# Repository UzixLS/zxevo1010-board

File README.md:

## ZXEVO.1010
10x10cm 2-layer PCB variant of [ZX Evolution](http://nedopc.com/zxevo/zxevo.php) project

Some random photos: [link](https://cloud.err200.net/index.php/s/73TR85tYZkMm8Ax?path=%2Fzxevo1010)

Tech specs:
- Fully compatible with ZX Evolution revC
- SD/microSD card slot
- PS/2 keyboard and mouse ports
- VGA video output
- VDAC2
- TSFM (mono output) powered by 2xYMF288
- [NeoGS](http://nedopc.com/gs/ngs.php)
- SounDrive (4-channel stereo covox)
- MIDI onboard synthesizer and output for external synthesizer
- WiFi ([ZiFi](http://zifi.vtrd.in/))
- RTC
- Tape input via 3.5 jack
- 1xDB-9 port for Sega-compatible joysticks
- USB Type C power supply
- Board optimized for G738 and G706 cases

### Changelog
#### Main PCB
* Rev.A - first release
* Rev.A1: - see [ERRATA](pcb_main/rev.A1/ERRATA.txt)!
    * enlarged ACEX's footprint
    * fixed IO led always on in baseconf - added C92 and D7
    * changed R66 from 390Ω to 2.2kΩ to reduce power led bightness
    * changed R52 and R58 from 27kΩ to 18kΩ for better VDAC2 mixing volume
    * slightly moved U18
    * some minor changes

#### Top PCB
* Rev.A - first release
* Rev.A1: - see [ERRATA](pcb_top/rev.A1/ERRATA.txt)!
    * added 51Ω R1 and R3 on DAC and MP3 clock signals to fix signal integrity issues
    * changed U9 from SN74LXC8T245PWR (which is unsuitable) to 74LVC245APW
    * changed R7 from 120Ω to 1kΩ to decrease LED brightness
    * changed R26 and R29 from 8.2kΩ to 18kΩ for better NeoGS mixing volume
    * changed R23 and R31 from 22kΩ to 15kΩ for better MIDI mixing volume
    * changed R65, R66, R67 and R68 from 8.2kΩ to 3.3kΩ for better PSG mixing volume (but this makes FM a unbalancy loud unfortunatelly)
    * added R50, R51, R61, C102, C103, C104 for VS10xx MP3 decoder
    * fixed swapped left-right sound channels
    * increased cutoff for CR2032 holder

### Useful software
* NedoOS (BaseConf): http://nedoos.ru/
* Wild Commander (TSConf): https://forum.tslabs.info/viewtopic.php?f=26&t=143
* ZiFi WiFi client (TSConf): http://zifi.vtrd.in/
* TSConf software library: https://prods.tslabs.info/
* Joystick configuration utility (TSConf): https://github.com/tslabs/zx-evo/tree/master/pentevo/soft/avrconf

### References
* ZX Evolution official site: http://nedopc.com/zxevo/zxevo.php

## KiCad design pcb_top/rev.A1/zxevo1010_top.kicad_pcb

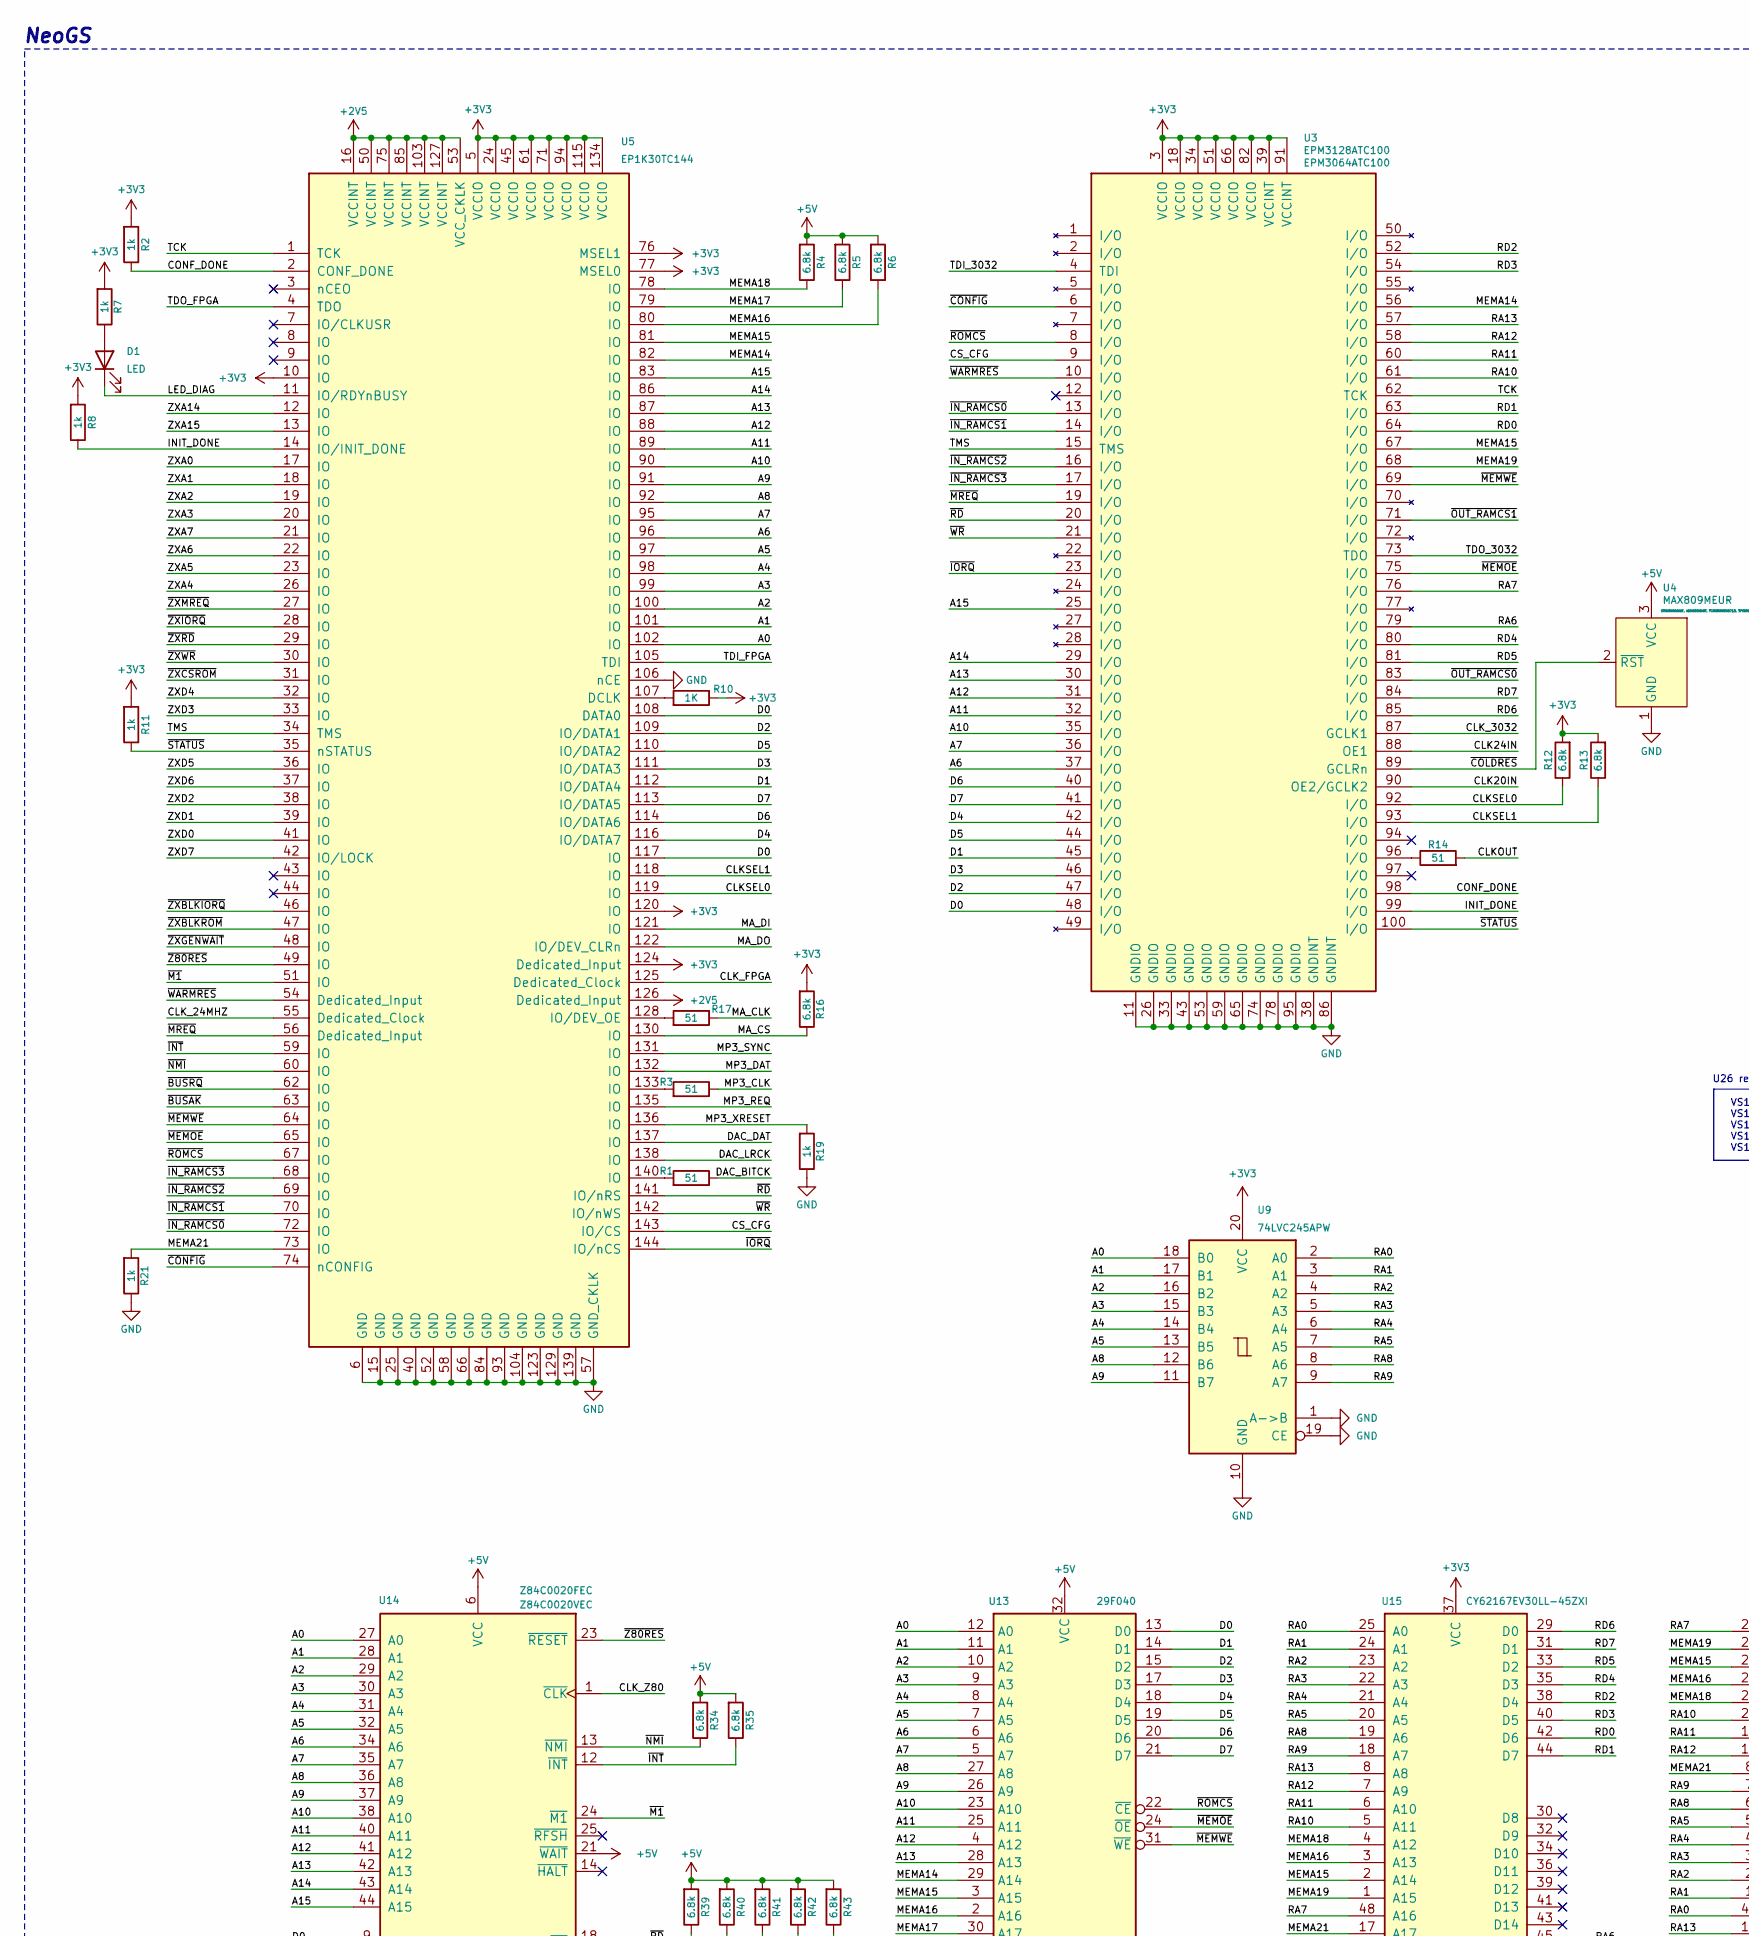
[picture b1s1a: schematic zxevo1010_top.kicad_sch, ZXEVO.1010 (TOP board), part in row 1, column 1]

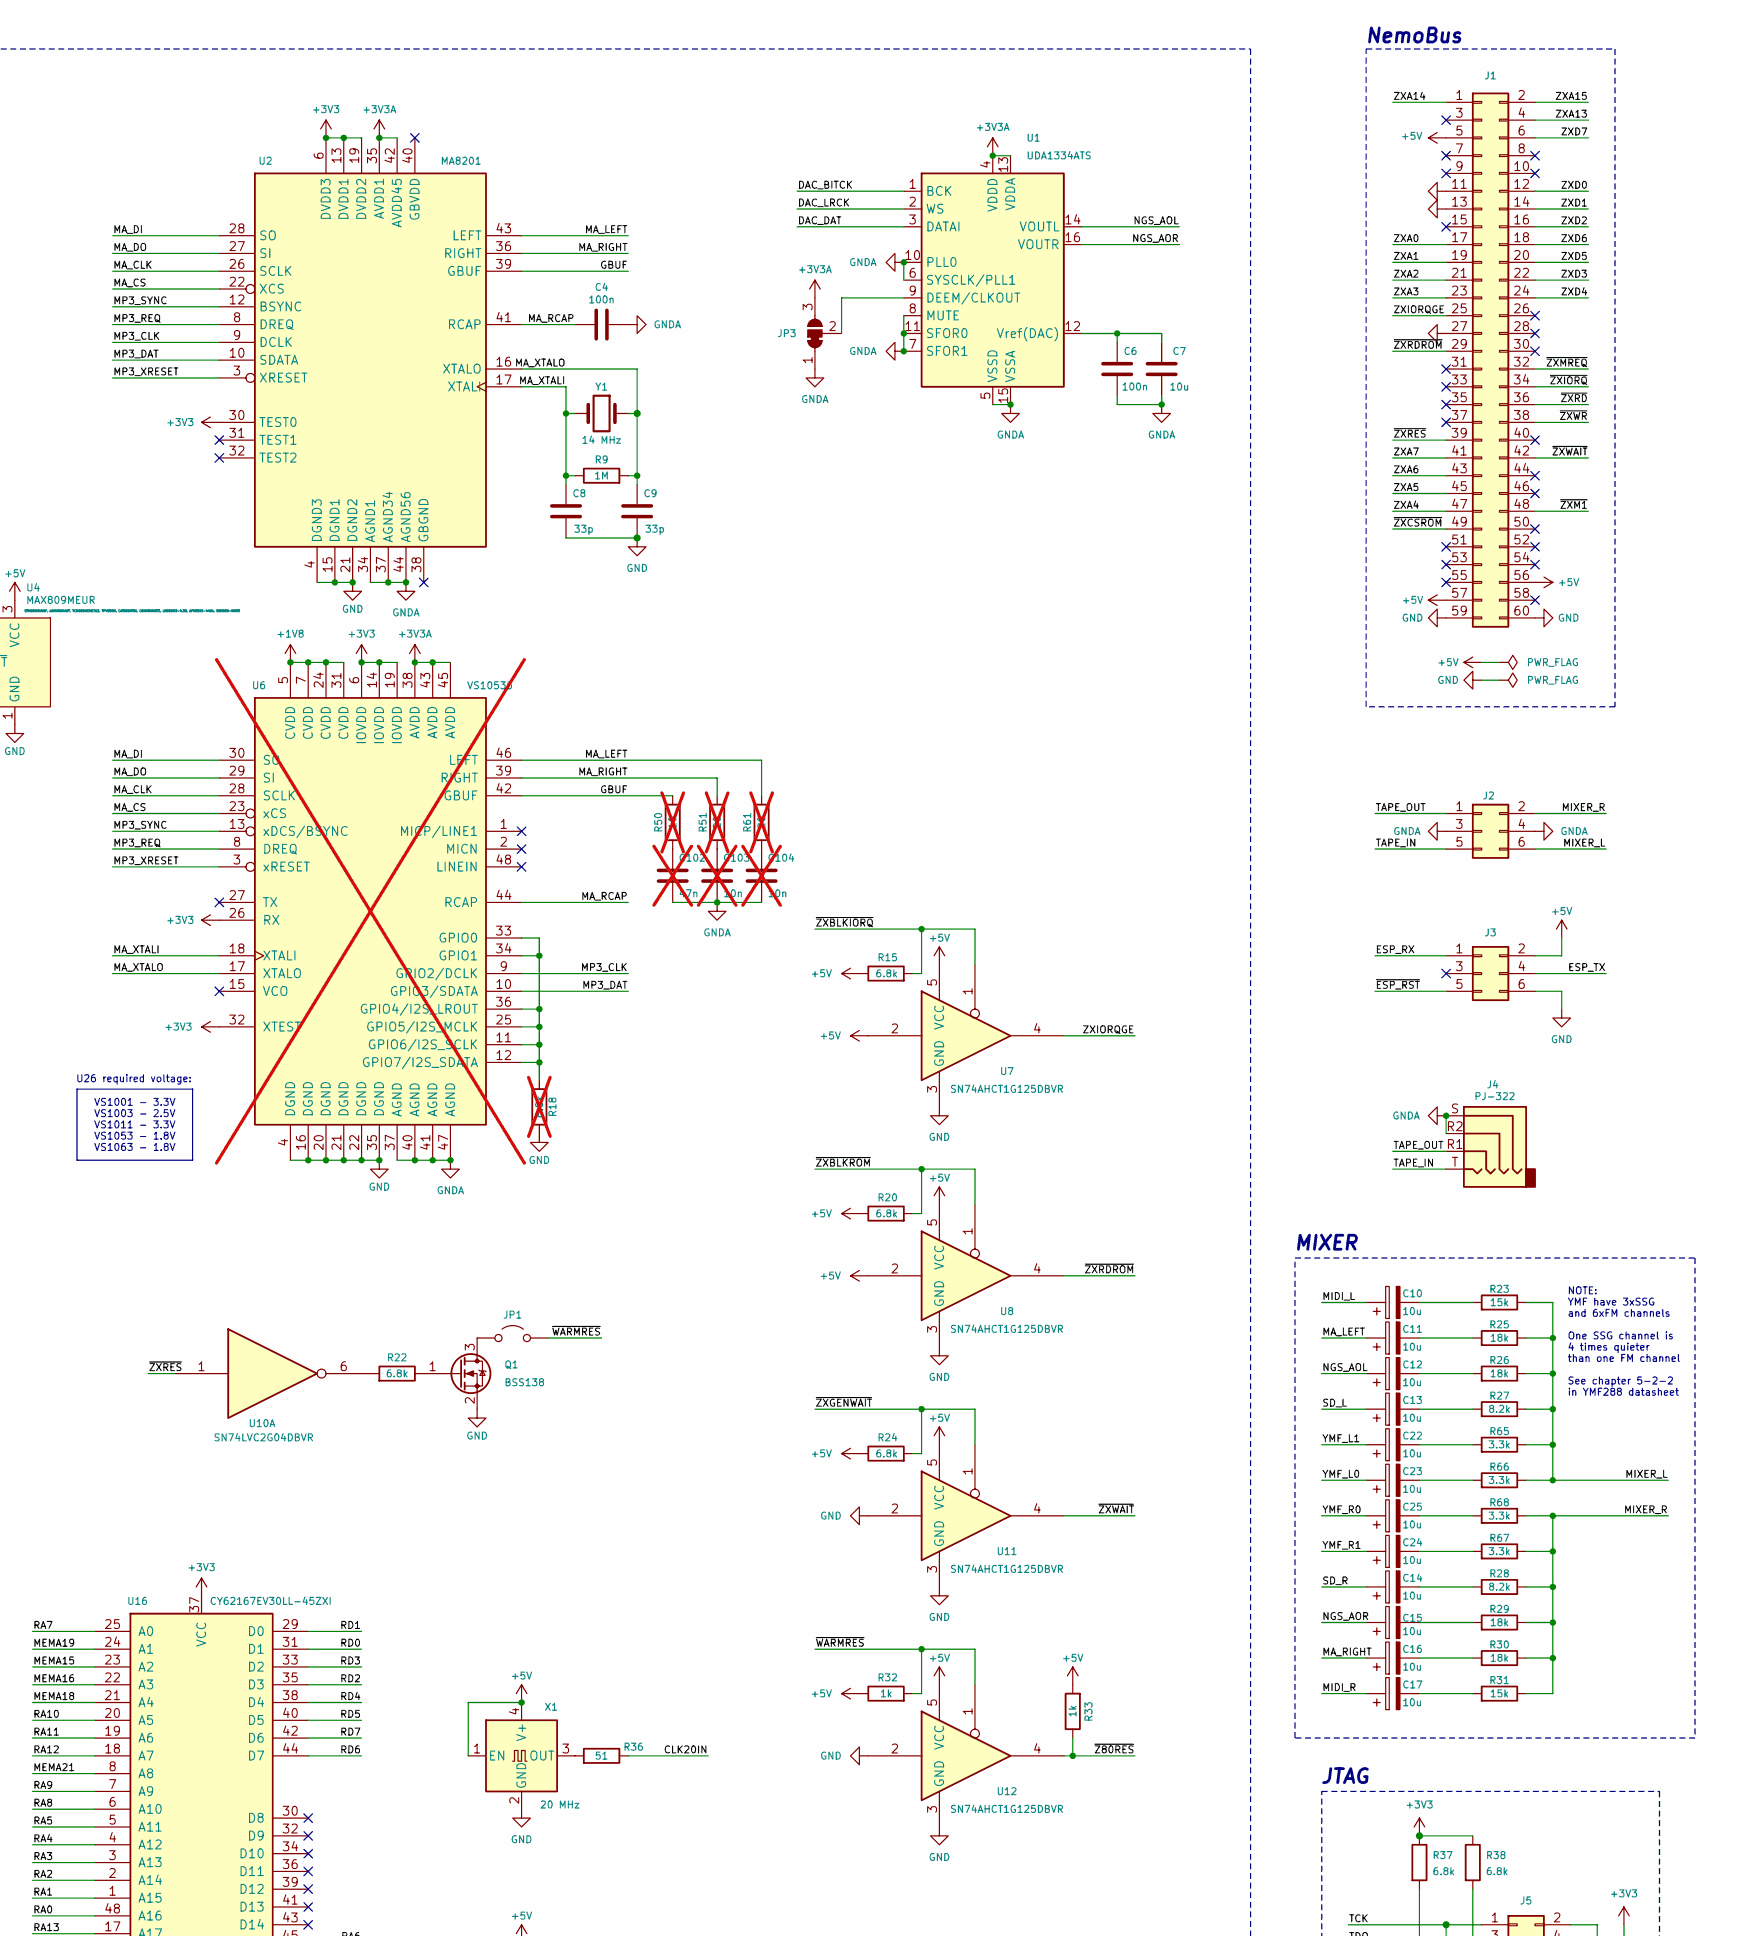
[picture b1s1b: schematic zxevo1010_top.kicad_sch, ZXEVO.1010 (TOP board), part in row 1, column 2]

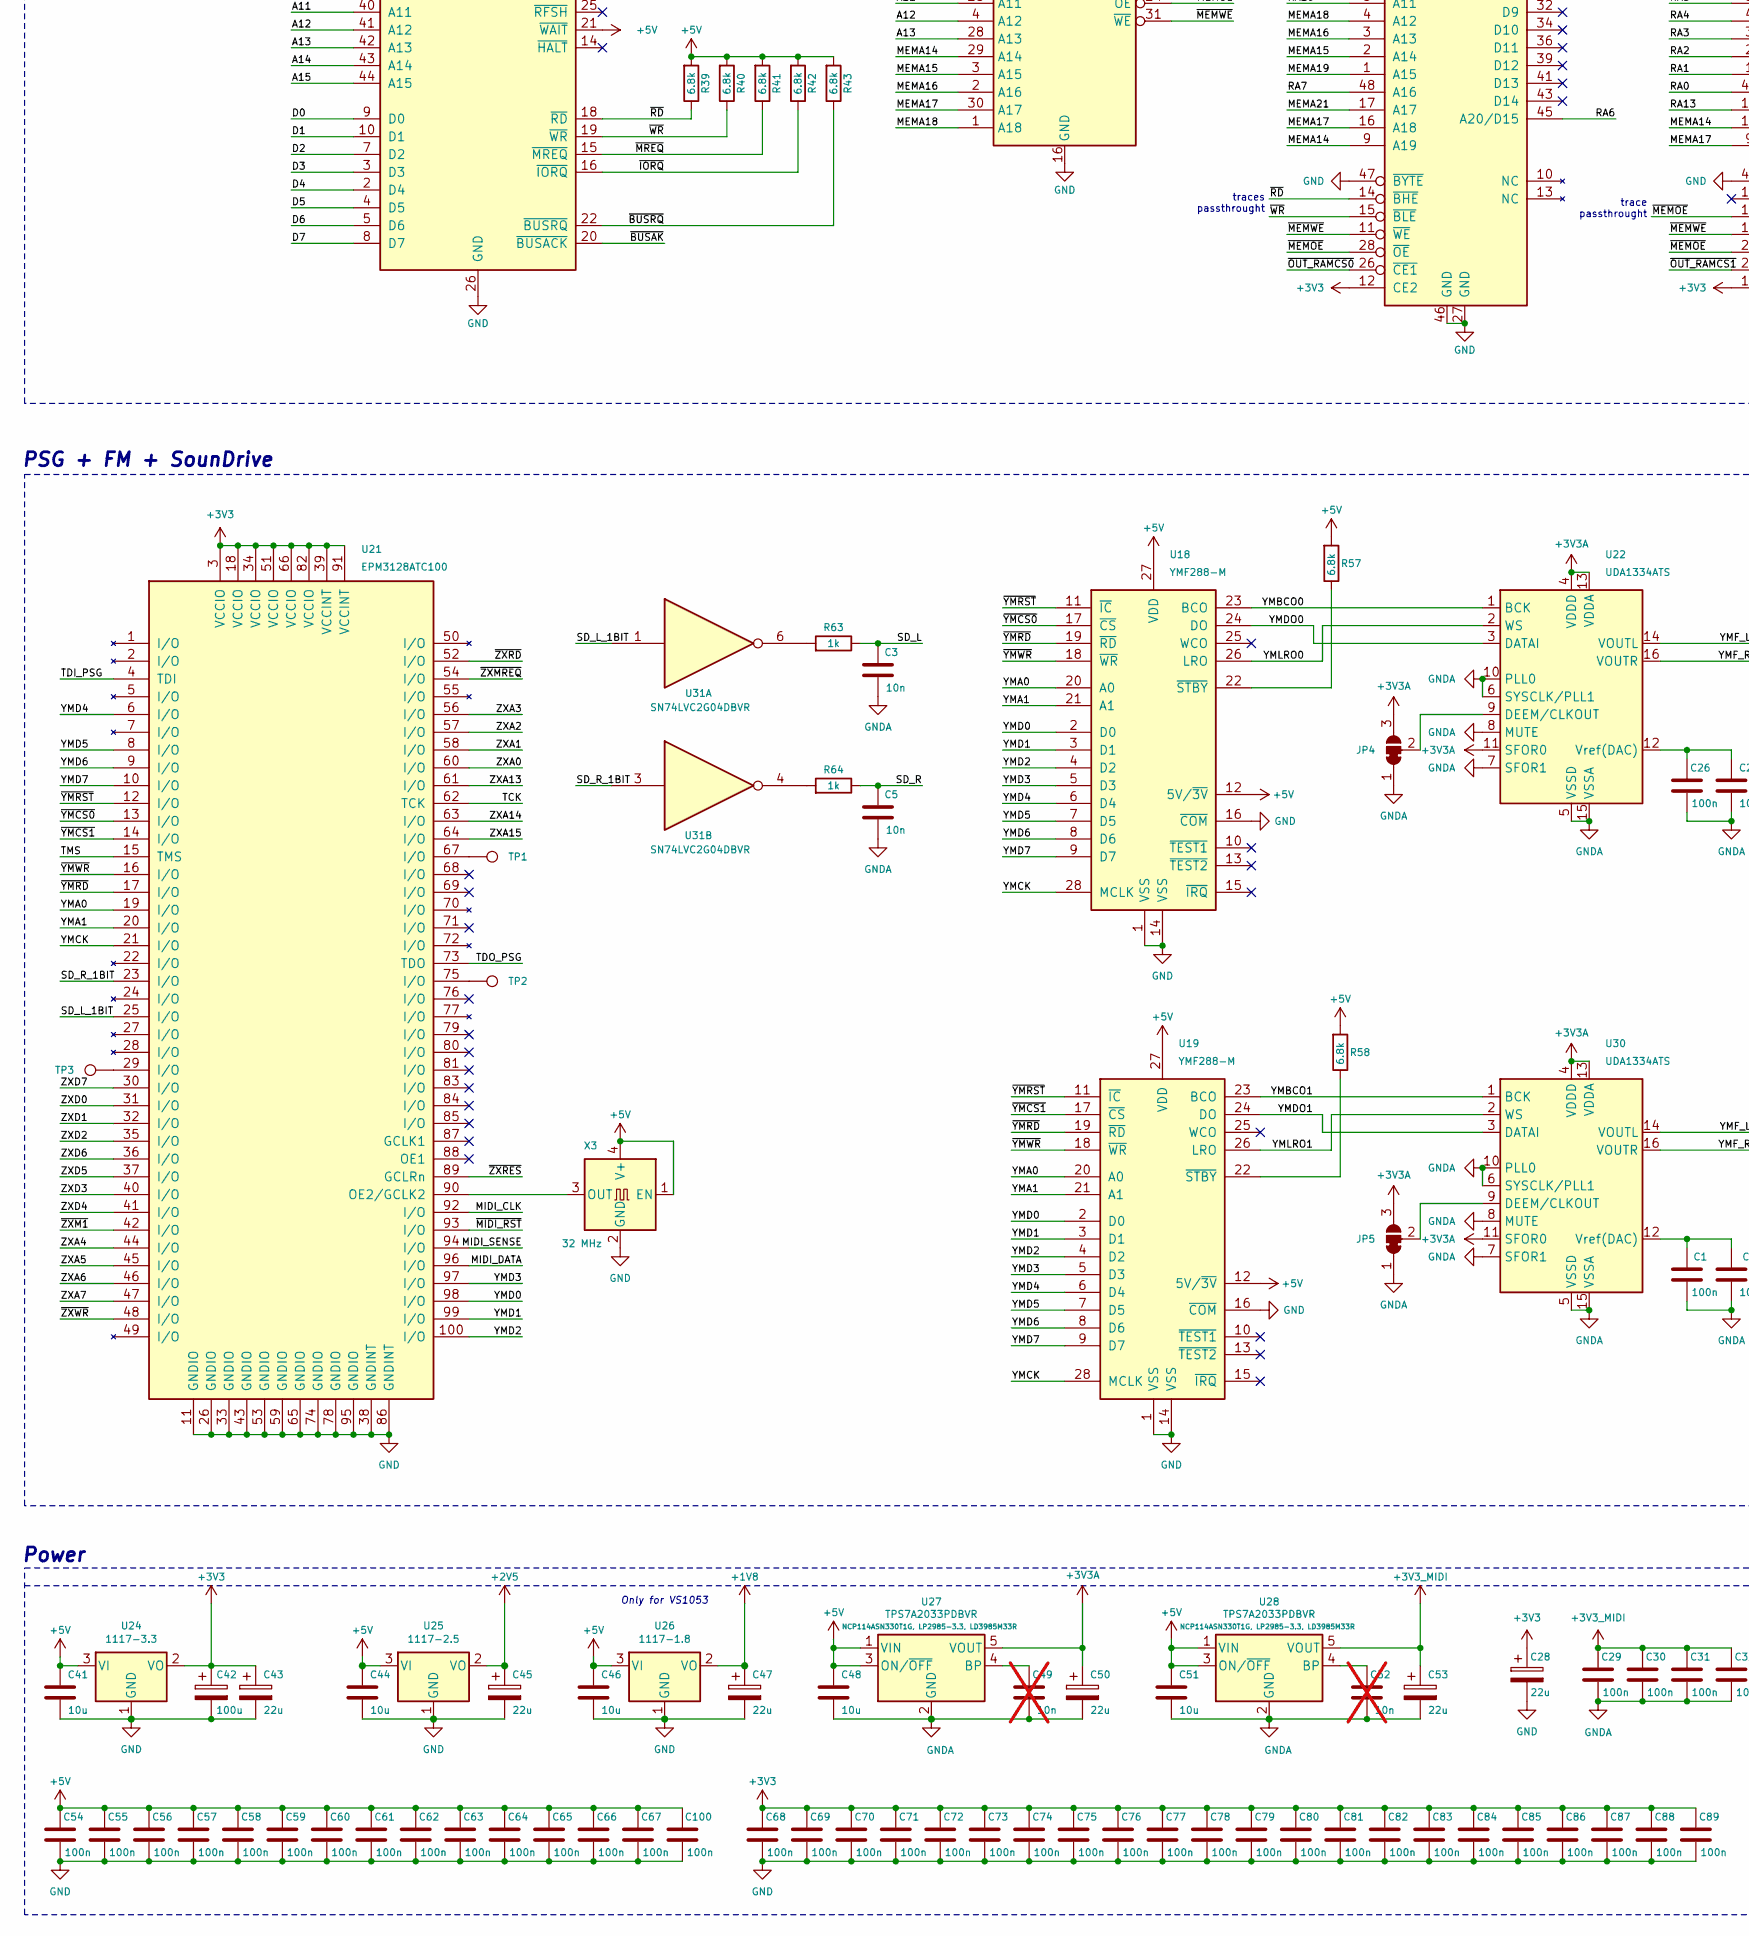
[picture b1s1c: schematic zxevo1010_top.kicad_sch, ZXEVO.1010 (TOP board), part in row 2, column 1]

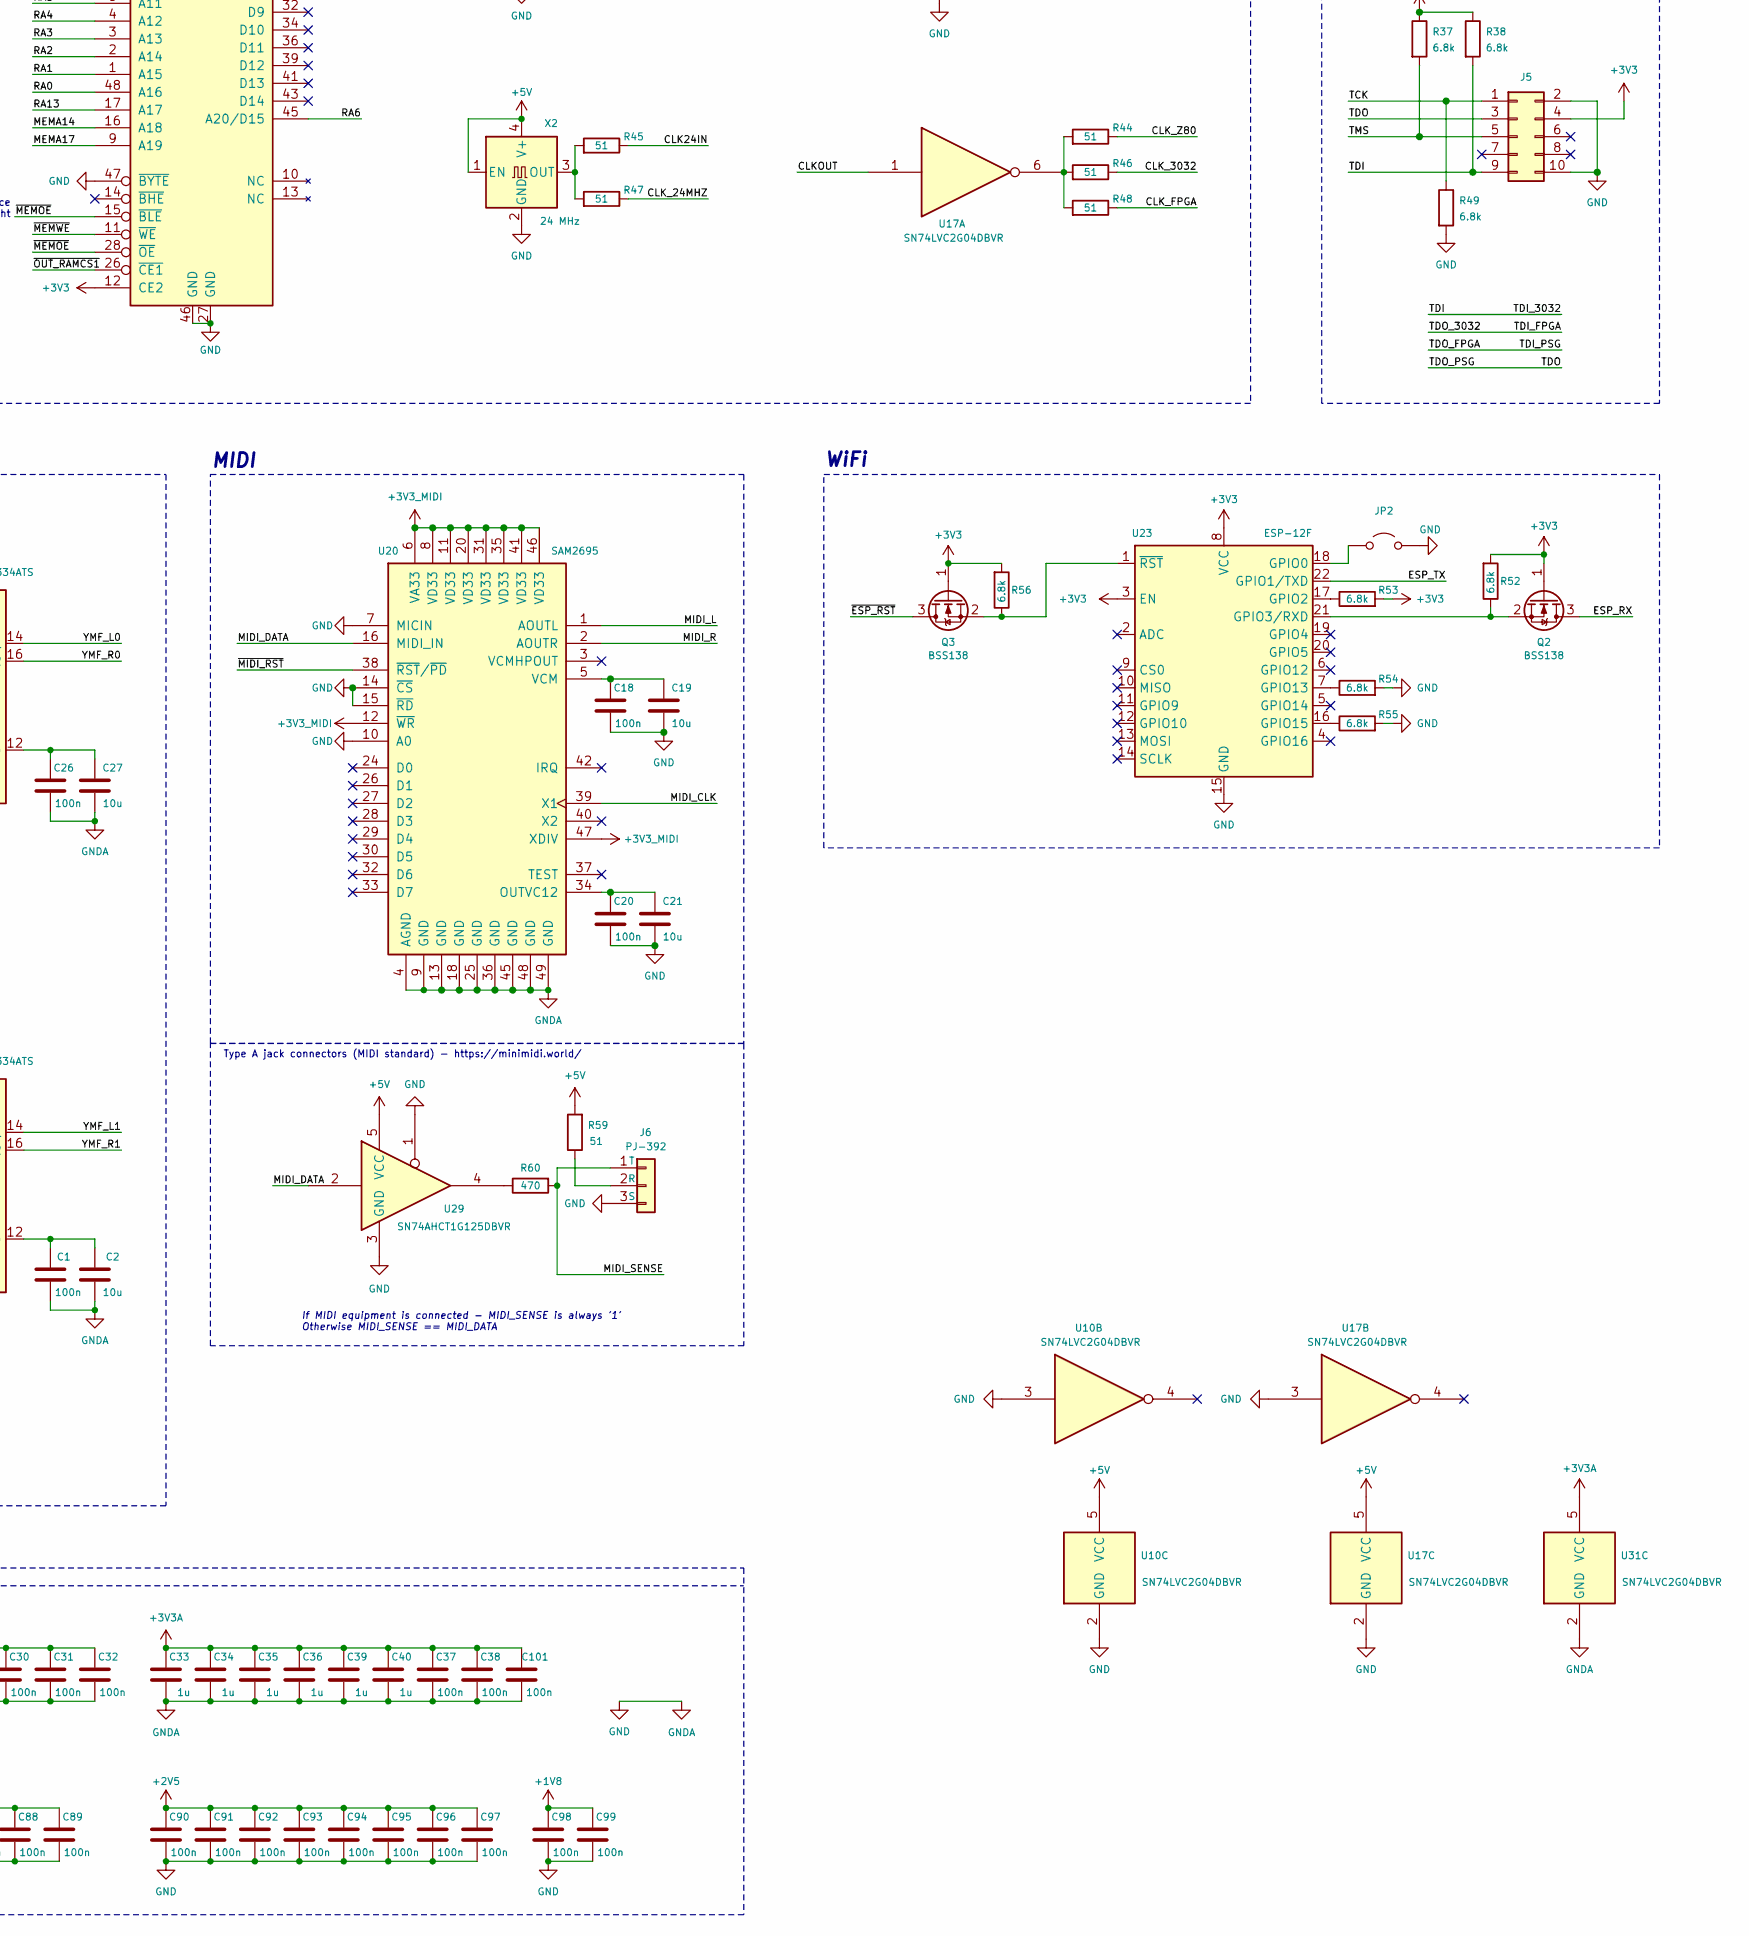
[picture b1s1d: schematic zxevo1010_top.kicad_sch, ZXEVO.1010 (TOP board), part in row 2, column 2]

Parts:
C1, C4, C6, C18, C20, C26, C29, C30, C31, C32, C37, C38, C54, C55, C56, C57, C58, C59, C60, C61, C62, C63, C64, C65, C66, C67, C68, C69, C70, C71, C72, C73, C74, C75, C76, C85, C86, C87, C88, C89, C98, C99, C100, C101: 100n; C_0603_1608Metric_Pad1.08x0.95mm_HandSolder
C2, C7, C19, C21, C27, C41, C44, C46, C48, C51: 10u; C_0805_2012Metric_Pad1.18x1.45mm_HandSolder
C3, C5: 10n; C_0603_1608Metric_Pad1.08x0.95mm_HandSolder
C8, C9: 33p; C_0603_1608Metric_Pad1.08x0.95mm_HandSolder
C10, C11, C12, C13, C14, C15, C16, C17, C22, C23, C24, C25: 10u; CP_EIA-3216-18_Kemet-A_Pad1.58x1.35mm_HandSolder
C28, C43, C45, C47, C50, C53: 22u; CP_EIA-3216-18_Kemet-A_Pad1.58x1.35mm_HandSolder
C33, C34, C35, C36, C39, C40: 1u; C_0603_1608Metric_Pad1.08x0.95mm_HandSolder
C42: 100u; CP_EIA-6032-28_Kemet-C_Pad2.25x2.35mm_HandSolder
C49, C52, C103, C104: 10n; C_0603_1608Metric_Pad1.08x0.95mm_HandSolder; not fitted
C77, C78, C79, C80, C81, C82, C83, C84, C90, C91, C92, C93, C94, C95, C96, C97: 100n; C_0805_2012Metric_Pad1.18x1.45mm_HandSolder
C102: 47n; C_0603_1608Metric_Pad1.08x0.95mm_HandSolder; not fitted
D1: LED; LED_0603_1608Metric_Pad1.05x0.95mm_HandSolder
J1: Conn_02x30_Row_Letter_First; PinHeader_2x30_P2.54mm_Vertical
J2, J3: Conn_02x05_Odd_Even; PinSocket_2x03_P2.54mm_Vertical
J4: PJ-322
J5: Conn_02x05_Odd_Even; PinHeader_2x05_P2.54mm_Vertical
J6: PJ-392; PinHeader_1x03_P2.54mm_Vertical
JP1, JP2: Jumper; PinHeader_1x02_P2.54mm_Vertical
JP3, JP4, JP5: SolderJumper_3_Bridged12; SolderJumper-3_P1.3mm_Bridged12_RoundedPad1.0x1.5mm
Q1, Q2, Q3: BSS138; SOT-23
R1, R3, R14, R17, R36, R44, R45, R46, R47, R48, R59: 51; R_0603_1608Metric_Pad0.98x0.95mm_HandSolder
R2, R7, R8, R11, R19, R21, R32, R33, R63, R64: 1k; R_0603_1608Metric_Pad0.98x0.95mm_HandSolder
R4, R5, R6, R12, R13, R15, R16, R20, R22, R24, R34, R35, R37, R38, R39, R40, R41, R42, R43, R49, R52, R53, R54, R55, R56, R57, R58: 6.8k; R_0603_1608Metric_Pad0.98x0.95mm_HandSolder
R9: 1M; R_0603_1608Metric_Pad0.98x0.95mm_HandSolder
R10: 1K; R_0603_1608Metric_Pad0.98x0.95mm_HandSolder
R18: 6.8k; R_0603_1608Metric_Pad0.98x0.95mm_HandSolder; not fitted
R23, R31: 15k; R_0603_1608Metric_Pad0.98x0.95mm_HandSolder
R25, R26, R29, R30: 18k; R_0603_1608Metric_Pad0.98x0.95mm_HandSolder
R27, R28: 8.2k; R_0603_1608Metric_Pad0.98x0.95mm_HandSolder
R50: 10; R_0603_1608Metric_Pad0.98x0.95mm_HandSolder; not fitted
R51, R61: 20; R_0603_1608Metric_Pad0.98x0.95mm_HandSolder; not fitted
R60: 470; R_0603_1608Metric_Pad0.98x0.95mm_HandSolder
R65, R66, R67, R68: 3.3k; R_0603_1608Metric_Pad0.98x0.95mm_HandSolder
TP1, TP2, TP3: TestPoint; TestPoint_Pad_D1.0mm
U1, U22, U30: UDA1334ATS; SSOP-16_4.4x5.2mm_P0.65mm
U2: MA8201; MQFP-44_10x10mm_P0.8mm
U3, U21: EPM3128ATC100; TQFP-100_14x14mm_P0.5mm
U4: MAX809MEUR; SOT-23
U5: EP1K30TC144; TQFP-144_20x20mm_P0.5mm
U6: VS1053b; LQFP-48_7x7mm_P0.5mm; not fitted
U7, U8, U11, U12, U29: SN74AHCT1G125DBVR; SOT-23-5_HandSoldering
U9: 74LVC245APW; TSSOP-20_4.4x6.5mm_P0.65mm
U10, U17, U31: SN74LVC2G04DBVR; SOT-23-6_Handsoldering
U13: 29F040; PLCC-32_11.4x14.0mm_P1.27mm-longpads
U14: Z84C0020FEC; Z80_FEC_VEC
U15, U16: CY62167EV30LL-45ZXI; TSOP-I-48_18.4x12mm_P0.5mm
U18, U19: YMF288-M; SOP-28_8.4x18.16mm_P1.27mm
U20: SAM2695; QFN-48-1EP_6x6mm_P0.4mm_EP4.2x4.2mm
U23: ESP-12F; ESP-12E
U24: 1117-3.3; SOT-223-3_TabPin2
U25: 1117-2.5; SOT-223-3_TabPin2
U26: 1117-1.8; SOT-223-3_TabPin2
U27, U28: TPS7A2033PDBVR; SOT-23-5_HandSoldering
X1: 20 MHz; Oscillator_SMD_7050_7.0x5.0mm
X2: 24 MHz; Oscillator_SMD_7050_7.0x5.0mm
X3: 32 MHz; Oscillator_SMD_7050_7.0x5.0mm
Y1: 14 MHz; Crystal_HC49-4H_Vertical

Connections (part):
+1V8: C47.1, C98.2, C99.2, U6.5 (CVDD), U6.7 (CVDD), U6.24 (CVDD), U6.31 (CVDD), U26.2 (VO)
+2V5: C45.1, C90.2, C91.2, C92.2, C93.2, C94.2, C95.2, C96.2, C97.2, U5.16 (VCCINT), U5.50 (VCCINT), U5.53 (VCC_CKLK), U5.75 (VCCINT), U5.85 (VCCINT), U5.103 (VCCINT), U5.126 (Dedicated_Input), U5.127 (VCCINT), U25.2 (VO)
+3V3: C28.1, C42.1, C43.1, C68.2, C69.2, C70.2, C71.2, C72.2, C73.2, C74.2, C75.2, C76.2, C77.2, C78.2, C79.2, C80.2, C81.2, C82.2, C83.2, C84.2, C85.2, C86.2, C87.2, C88.2, C89.2, J5.4, Q2.1 (G), Q3.1 (G), R2.2, R7.2, R8.2, R10.1, R11.2, R12.2, R13.2, R16.2, R37.1, R38.1, R52.2, R53.2, R56.2, U2.6 (DVDD3), U2.13 (DVDD1), U2.19 (DVDD2), U2.30 (TEST0), U3.3 (VCCIO), U3.18 (VCCIO), U3.34 (VCCIO), U3.39 (VCCINT), U3.51 (VCCIO), U3.66 (VCCIO), U3.82 (VCCIO), U3.91 (VCCINT), U5.5 (VCCIO), U5.10 (IO), U5.24 (VCCIO), U5.45 (VCCIO), U5.61 (VCCIO), U5.71 (VCCIO), U5.76 (MSEL1), U5.77 (MSEL0), U5.94 (VCCIO), U5.115 (VCCIO), U5.120 (IO), U5.124 (Dedicated_Input), U5.134 (VCCIO), U6.6 (IOVDD), U6.14 (IOVDD), U6.19 (IOVDD), U6.26 (RX), U6.32 (XTEST), U9.20 (VCC), U15.12 (CE2), U15.37 (VCC), U16.12 (CE2), U16.37 (VCC), U21.3 (VCCIO), U21.18 (VCCIO), U21.34 (VCCIO), U21.39 (VCCINT), U21.51 (VCCIO), U21.66 (VCCIO), U21.82 (VCCIO), U21.91 (VCCINT), U23.3 (EN), U23.8 (VCC), U24.2 (VO)
+3V3A: C33.2, C34.2, C35.2, C36.2, C37.2, C38.2, C39.2, C40.2, C50.1, C101.2, JP3.3 (B), JP4.3 (B), JP5.3 (B), U1.4 (VDDD), U1.13 (VDDA), U2.35 (AVDD1), U2.42 (AVDD45), U6.38 (AVDD), U6.43 (AVDD), U6.45 (AVDD), U22.4 (VDDD), U22.11 (SFOR0), U22.13 (VDDA), U27.5 (VOUT), U30.4 (VDDD), U30.11 (SFOR0), U30.13 (VDDA), U31.5 (VCC)
+3V3_MIDI: C29.2, C30.2, C31.2, C32.2, C53.1, U20.6 (VA33), U20.8 (VD33), U20.11 (VD33), U20.12 (~WR), U20.20 (VD33), U20.31 (VD33), U20.35 (VD33), U20.41 (VD33), U20.46 (VD33), U20.47 (XDIV), U28.5 (VOUT)
+5V: C41.2, C44.2, C46.2, C48.2, C51.2, C54.2, C55.2, C56.2, C57.2, C58.2, C59.2, C60.2, C61.2, C62.2, C63.2, C64.2, C65.2, C66.2, C67.2, C100.2, J1.5, J1.56, J1.57, J3.2, R4.2, R5.2, R6.2, R15.1, R20.1, R24.1, R32.1, R33.2, R34.2, R35.2, R39.2, R40.2, R41.2, R42.2, R43.2, R57.2, R58.2, R59.2, U4.3 (VCC), U7.2, U7.5 (VCC), U8.2, U8.5 (VCC), U10.5 (VCC), U11.5 (VCC), U12.5 (VCC), U13.32 (VCC), U14.6 (VCC), U14.21 (~WAIT), U17.5 (VCC), U18.12 (5V/~3V), U18.27 (VDD), U19.12 (5V/~3V), U19.27 (VDD), U24.3 (VI), U25.3 (VI), U26.3 (VI), U27.1 (VIN), U27.3 (ON/~OFF), U28.1 (VIN), U28.3 (ON/~OFF), U29.5 (VCC), X1.1 (EN), X1.4 (V+), X2.1 (EN), X2.4 (V+), X3.1 (EN), X3.4 (V+)
/A0: U5.102 (IO), U9.18 (B0), U13.12 (A0), U14.27 (A0)
/A1: U5.101 (IO), U9.17 (B1), U13.11 (A1), U14.28 (A1)
/A2: U5.100 (IO), U9.16 (B2), U13.10 (A2), U14.29 (A2)
/A3: U5.99 (IO), U9.15 (B3), U13.9 (A3), U14.30 (A3)
/A4: U5.98 (IO), U9.14 (B4), U13.8 (A4), U14.31 (A4)
/A5: U5.97 (IO), U9.13 (B5), U13.7 (A5), U14.32 (A5)
/A6: U3.37 (I/O), U5.96 (IO), U13.6 (A6), U14.34 (A6)
/A7: U3.36 (I/O), U5.95 (IO), U13.5 (A7), U14.35 (A7)
/A8: U5.92 (IO), U9.12 (B6), U13.27 (A8), U14.36 (A8)
/A9: U5.91 (IO), U9.11 (B7), U13.26 (A9), U14.37 (A9)
/A10: U3.35 (I/O), U5.90 (IO), U13.23 (A10), U14.38 (A10)
/A11: U3.32 (I/O), U5.89 (IO), U13.25 (A11), U14.40 (A11)
/A12: U3.31 (I/O), U5.88 (IO), U13.4 (A12), U14.41 (A12)
/A13: U3.30 (I/O), U5.87 (IO), U13.28 (A13), U14.42 (A13)
/A14: U3.29 (I/O), U5.86 (IO), U14.43 (A14)
/A15: U3.25 (I/O), U5.83 (IO), U14.44 (A15)
/CLK20IN: R36.1, U3.90 (OE2/GCLK2)
/CLK24IN: R45.1, U3.88 (OE1)
/CLKOUT: R14.2, U17.1
/CLKSEL0: R12.1, U3.92 (I/O), U5.119 (IO)
/CLKSEL1: R13.1, U3.93 (I/O), U5.118 (IO)
/CLK_24MHZ: R47.1, U5.55 (Dedicated_Clock)
/CLK_3032: R46.1, U3.87 (GCLK1)
/CLK_FPGA: R48.1, U5.125 (Dedicated_Clock)
/CLK_Z80: R44.1, U14.1 (~CLK)
/CONF_DONE: R2.1, U3.98 (I/O), U5.2 (CONF_DONE)
/CS_CFG: U3.9 (I/O), U5.143 (IO/CS)
/D0: U3.48 (I/O), U5.108 (DATA0), U5.117 (IO), U13.13 (D0), U14.9 (D0)
/D1: U3.45 (I/O), U5.112 (IO/DATA4), U13.14 (D1), U14.10 (D1)
/D2: U3.47 (I/O), U5.109 (IO/DATA1), U13.15 (D2), U14.7 (D2)
/D3: U3.46 (I/O), U5.111 (IO/DATA3), U13.17 (D3), U14.3 (D3)
/D4: U3.42 (I/O), U5.116 (IO/DATA7), U13.18 (D4), U14.2 (D4)
/D5: U3.44 (I/O), U5.110 (IO/DATA2), U13.19 (D5), U14.4 (D5)
/D6: U3.40 (I/O), U5.114 (IO/DATA6), U13.20 (D6), U14.5 (D6)
/D7: U3.41 (I/O), U5.113 (IO/DATA5), U13.21 (D7), U14.8 (D7)
/DAC_BITCK: R1.1, U1.1 (BCK)
/DAC_DAT: U1.3 (DATAI), U5.137 (IO)
/DAC_LRCK: U1.2 (WS), U5.138 (IO)
/ESP_RX: J3.1, Q2.3 (D)
/ESP_TX: J3.4, U23.22 (GPIO1/TXD)
/GBUF: R50.2, U2.39 (GBUF), U6.42 (GBUF)
/INIT_DONE: R8.1, U3.99 (I/O), U5.14 (IO/INIT_DONE)
/LED_DIAG: D1.1 (K), U5.11 (IO/RDYnBUSY)
/MA_CLK: R17.1, U2.26 (SCLK), U6.28 (SCLK)
/MA_CS: R16.1, U2.22 (XCS), U5.130 (IO), U6.23 (xCS)
/MA_DI: U2.28 (SO), U5.121 (IO), U6.30 (SO)
/MA_DO: U2.27 (SI), U5.122 (IO/DEV_CLRn), U6.29 (SI)
/MA_LEFT: C11.1, R61.2, U2.43 (LEFT), U6.46 (LEFT)
/MA_RCAP: C4.1, U2.41 (RCAP), U6.44 (RCAP)
/MA_RIGHT: C16.1, R51.2, U2.36 (RIGHT), U6.39 (RIGHT)
/MA_XTALI: C8.2, R9.1, U2.17 (XTALI), U6.18 (XTALI), Y1.2
/MA_XTALO: C9.2, R9.2, U2.16 (XTALO), U6.17 (XTALO), Y1.1
/MEMA14: U3.56 (I/O), U5.82 (IO), U13.29 (A14), U15.9 (A19), U16.16 (A18)
/MEMA15: U3.67 (I/O), U5.81 (IO), U13.3 (A15), U15.2 (A14), U16.23 (A2)
/MEMA16: R6.1, U5.80 (IO), U13.2 (A16), U15.3 (A13), U16.22 (A3)
/MEMA17: R5.1, U5.79 (IO), U13.30 (A17), U15.16 (A18), U16.9 (A19)
/MEMA18: R4.1, U5.78 (IO), U13.1 (A18), U15.4 (A12), U16.21 (A4)
/MEMA19: U3.68 (I/O), U15.1 (A15), U16.24 (A1)
/MEMA21: R21.2, U5.73 (IO), U15.17 (A17), U16.8 (A8)
/MIDI_CLK: U20.39 (X1), U21.92 (I/O)
/MIDI_DATA: U20.16 (MIDI_IN), U21.96 (I/O), U29.2
/MIDI_L: C10.1, U20.1 (AOUTL)
/MIDI_R: C17.1, U20.2 (AOUTR)
/MIDI_SENSE: J6.1, R60.2, U21.94 (I/O)
/MIXER_L: J2.6, R23.1, R25.1, R26.1, R27.1, R65.1, R66.1
/MIXER_R: J2.2, R28.1, R29.1, R30.1, R31.1, R67.1, R68.1
/MP3_CLK: R3.1, U2.9 (DCLK), U6.9 (GPIO2/DCLK)
/MP3_DAT: U2.10 (SDATA), U5.132 (IO), U6.10 (GPIO3/SDATA)
/MP3_REQ: U2.8 (DREQ), U5.135 (IO), U6.8 (DREQ)
/MP3_SYNC: U2.12 (BSYNC), U5.131 (IO), U6.13 (xDCS/BSYNC)
/MP3_XRESET: R19.2, U2.3 (XRESET), U5.136 (IO), U6.3 (xRESET)
/NGS_AOL: C12.1, U1.14 (VOUTL)
/NGS_AOR: C15.1, U1.16 (VOUTR)
/RA0: U9.2 (A0), U15.25 (A0), U16.48 (A16)
/RA1: U9.3 (A1), U15.24 (A1), U16.1 (A15)
/RA2: U9.4 (A2), U15.23 (A2), U16.2 (A14)
/RA3: U9.5 (A3), U15.22 (A3), U16.3 (A13)
/RA4: U9.6 (A4), U15.21 (A4), U16.4 (A12)
/RA5: U9.7 (A5), U15.20 (A5), U16.5 (A11)
/RA6: U3.79 (I/O), U15.45 (A20/D15), U16.45 (A20/D15)
/RA7: U3.76 (I/O), U15.48 (A16), U16.25 (A0)
/RA8: U9.8 (A6), U15.19 (A6), U16.6 (A10)
/RA9: U9.9 (A7), U15.18 (A7), U16.7 (A9)
/RA10: U3.61 (I/O), U15.5 (A11), U16.20 (A5)
/RA11: U3.60 (I/O), U15.6 (A10), U16.19 (A6)
/RA12: U3.58 (I/O), U15.7 (A9), U16.18 (A7)
/RA13: U3.57 (I/O), U15.8 (A8), U16.17 (A17)
/RD0: U3.64 (I/O), U15.42 (D6), U16.31 (D1)
/RD1: U3.63 (I/O), U15.44 (D7), U16.29 (D0)
/RD2: U3.52 (I/O), U15.38 (D4), U16.35 (D3)
/RD3: U3.54 (I/O), U15.40 (D5), U16.33 (D2)
/RD4: U3.80 (I/O), U15.35 (D3), U16.38 (D4)
/RD5: U3.81 (I/O), U15.33 (D2), U16.40 (D5)
/RD6: U3.85 (I/O), U15.29 (D0), U16.44 (D7)
/RD7: U3.84 (I/O), U15.31 (D1), U16.42 (D6)
/SD_L: C3.2, C13.1, R63.1
/SD_L_1BIT: U21.25 (I/O), U31.1
/SD_R: C5.2, C14.1, R64.1
/SD_R_1BIT: U21.23 (I/O), U31.3
/TAPE_IN: J2.5, J4.T
/TAPE_OUT: J2.1, J4.R1
/TCK: J5.1, R49.1, U3.62 (TCK), U5.1 (TCK), U21.62 (TCK)
/TDI: J5.9, R38.2, U3.4 (TDI)
/TDI_FPGA: U3.73 (TDO), U5.105 (TDI)
/TDI_PSG: U5.4 (TDO), U21.4 (TDI)
/TDO: J5.3, U21.73 (TDO)
/TMS: J5.5, R37.2, U3.15 (TMS), U5.34 (TMS), U21.15 (TMS)
/YMA0: U18.20 (A0), U19.20 (A0), U21.19 (I/O)
/YMA1: U18.21 (A1), U19.21 (A1), U21.20 (I/O)
/YMBCO0: U18.23 (BCO), U22.1 (BCK)
/YMBCO1: U19.23 (BCO), U30.1 (BCK)
/YMCK: U18.28 (MCLK), U19.28 (MCLK), U21.21 (I/O)
/YMD0: U18.2 (D0), U19.2 (D0), U21.98 (I/O)
/YMD1: U18.3 (D1), U19.3 (D1), U21.99 (I/O)
/YMD2: U18.4 (D2), U19.4 (D2), U21.100 (I/O)
/YMD3: U18.5 (D3), U19.5 (D3), U21.97 (I/O)
/YMD4: U18.6 (D4), U19.6 (D4), U21.6 (I/O)
/YMD5: U18.7 (D5), U19.7 (D5), U21.8 (I/O)
/YMD6: U18.8 (D6), U19.8 (D6), U21.9 (I/O)
/YMD7: U18.9 (D7), U19.9 (D7), U21.10 (I/O)
/YMDO0: U18.24 (DO), U22.3 (DATAI)
/YMDO1: U19.24 (DO), U30.3 (DATAI)
/YMF_L0: C23.1, U22.14 (VOUTL)
/YMF_L1: C22.1, U30.14 (VOUTL)
/YMF_R0: C25.1, U22.16 (VOUTR)
/YMF_R1: C24.1, U30.16 (VOUTR)
/YMLRO0: U18.26 (LRO), U22.2 (WS)
/YMLRO1: U19.26 (LRO), U30.2 (WS)
/ZXA0: J1.17, U5.17 (IO), U21.60 (I/O)
/ZXA1: J1.19, U5.18 (IO), U21.58 (I/O)
/ZXA2: J1.21, U5.19 (IO), U21.57 (I/O)
/ZXA3: J1.23, U5.20 (IO), U21.56 (I/O)
/ZXA4: J1.47, U5.26 (IO), U21.44 (I/O)
/ZXA5: J1.45, U5.23 (IO), U21.45 (I/O)
/ZXA6: J1.43, U5.22 (IO), U21.46 (I/O)
/ZXA7: J1.41, U5.21 (IO), U21.47 (I/O)
/ZXA13: J1.4, U21.61 (I/O)
/ZXA14: J1.1, U5.12 (IO), U21.63 (I/O)
/ZXA15: J1.2, U5.13 (IO), U21.64 (I/O)
/ZXD0: J1.12, U5.41 (IO), U21.31 (I/O)
/ZXD1: J1.14, U5.39 (IO), U21.32 (I/O)
/ZXD2: J1.16, U5.38 (IO), U21.35 (I/O)
/ZXD3: J1.22, U5.33 (IO), U21.40 (I/O)
/ZXD4: J1.24, U5.32 (IO), U21.41 (I/O)
/ZXD5: J1.20, U5.36 (IO), U21.37 (I/O)
/ZXD6: J1.18, U5.37 (IO), U21.36 (I/O)
/ZXD7: J1.6, U5.42 (IO/LOCK), U21.30 (I/O)
/ZXIORQGE: J1.25, U7.4
/~BUSAK: U5.63 (IO), U14.20 (~BUSACK)
/~BUSRQ: R43.1, U5.62 (IO), U14.22 (~BUSRQ)
/~COLDRES: U3.89 (GCLRn), U4.2 (~RST)
/~CONFIG: U3.6 (I/O), U5.74 (nCONFIG)
/~ESP_RST: J3.5, Q3.3 (D)
/~INT: R35.1, U5.59 (IO), U14.12 (~INT)
/~IN_RAMCS0: U3.13 (I/O), U5.72 (IO)
/~IN_RAMCS1: U3.14 (I/O), U5.70 (IO)
/~IN_RAMCS2: U3.16 (I/O), U5.69 (IO)
/~IN_RAMCS3: U3.17 (I/O), U5.68 (IO)
/~IORQ: R42.1, U3.23 (I/O), U5.144 (IO/nCS), U14.16 (~IORQ)
/~M1: U5.51 (IO), U14.24 (~M1)
/~MEMOE: U3.75 (I/O), U5.65 (IO), U13.24 (~OE), U15.28 (~OE), U16.15 (~BLE), U16.28 (~OE)
/~MEMWE: U3.69 (I/O), U5.64 (IO), U13.31 (~WE), U15.11 (~WE), U16.11 (~WE)
/~MIDI_RST: U20.38 (~RST/~PD), U21.93 (I/O)
/~MREQ: R41.1, U3.19 (I/O), U5.56 (Dedicated_Input), U14.15 (~MREQ)
/~NMI: R34.1, U5.60 (IO), U14.13 (~NMI)
/~OUT_RAMCS0: U3.83 (I/O), U15.26 (~CE1)
/~OUT_RAMCS1: U3.71 (I/O), U16.26 (~CE1)
/~RD: R39.1, U3.20 (I/O), U5.141 (IO/nRS), U14.18 (~RD), U15.14 (~BHE)
/~ROMCS: U3.8 (I/O), U5.67 (IO), U13.22 (~CE)
/~STATUS: R11.1, U3.100 (I/O), U5.35 (nSTATUS)
/~WARMRES: JP1.2 (B), R32.2, U3.10 (I/O), U5.54 (Dedicated_Input), U12.1
/~WR: R40.1, U3.21 (I/O), U5.142 (IO/nWS), U14.19 (~WR), U15.15 (~BLE)
/~YMCS0: U18.17 (~CS), U21.13 (I/O)
/~YMCS1: U19.17 (~CS), U21.14 (I/O)
/~YMRD: U18.19 (~RD), U19.19 (~RD), U21.17 (I/O)
/~YMRST: U18.11 (~IC), U19.11 (~IC), U21.12 (I/O)
/~YMWR: U18.18 (~WR), U19.18 (~WR), U21.16 (I/O)
/~Z80RES: R33.1, U5.49 (IO), U12.4, U14.23 (~RESET)
/~ZXBLKIORQ: R15.2, U5.46 (IO), U7.1
/~ZXBLKROM: R20.2, U5.47 (IO), U8.1
/~ZXCSROM: J1.49, U5.31 (IO)
/~ZXGENWAIT: R24.2, U5.48 (IO), U11.1
/~ZXIORQ: J1.34, U5.28 (IO)
/~ZXM1: J1.48, U21.42 (I/O)
/~ZXMREQ: J1.32, U5.27 (IO), U21.54 (I/O)
/~ZXRDROM: J1.29, U8.4
/~ZXRD: J1.36, U5.29 (IO), U21.52 (I/O)
/~ZXRES: J1.39, U10.1, U21.89 (GCLRn)
/~ZXWAIT: J1.42, U11.4
/~ZXWR: J1.38, U5.30 (IO), U21.48 (I/O)
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
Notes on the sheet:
VS1001 - 3.3V VS1003 - 2.5V VS1011 - 3.3V VS1053 - 1.8V VS1063 - 1.8V
WiFi
Type A jack connectors (MIDI standard) - https://minimidi.world/
MIDI
traces passthrought
NOTE: YMF have 3xSSG and 6xFM channels One SSG channel is 4 times quieter than one FM channel See chapter 5-2-2 in YMF288 datasheet
NeoGS
U26 required voltage:
JTAG
PSG + FM + SounDrive
If MIDI equipment is connected - MIDI_SENSE is always '1' Otherwise MIDI_SENSE == MIDI_DATA
Power
Only for VS1053
trace passthrought
NemoBus
MIXER
